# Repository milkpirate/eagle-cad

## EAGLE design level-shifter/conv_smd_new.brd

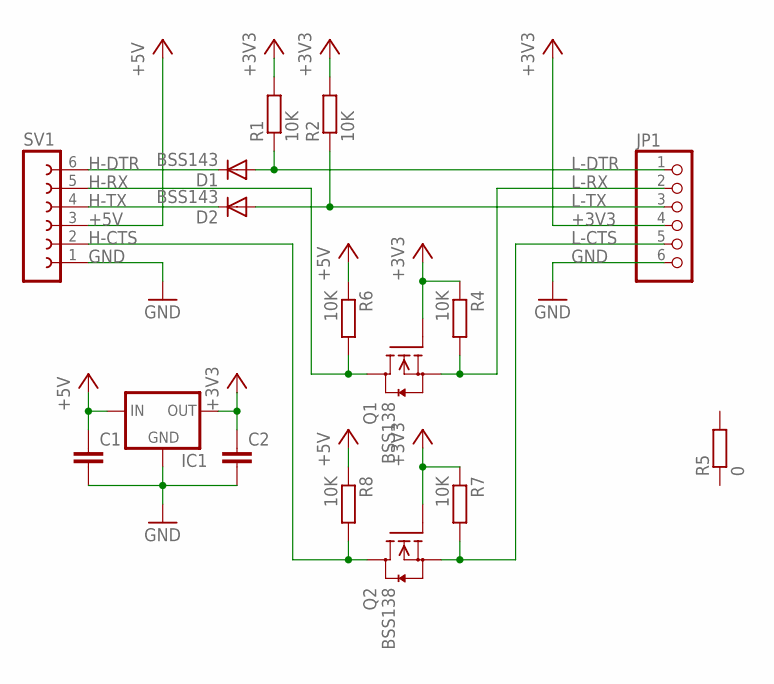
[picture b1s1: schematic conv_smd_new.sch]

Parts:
C1, C2: C-EUC0805; C0805
D1, D2: BSS143; SOD80C
IC1: MCP1700_SOT-32; SOT23
JP1: PINHD-1X6/90; 1X06/90
Q1, Q2: BSS138; SOT23
R1, R2, R4, R6, R7, R8: 10K; M0805
R5: 0; M1206
SV1: FE06W

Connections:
+3V3: C2.1, IC1.2 (OUT), JP1.4, Q1.1 (G), Q2.1 (G), R1.2, R2.2, R4.1, R7.1
+5V: C1.1, IC1.3 (IN), R6.1, R8.1, SV1.3
GND: C1.2, C2.2, IC1.1 (GND), JP1.6, SV1.1
H-CTS: Q2.3 (D), R8.2, SV1.2
H-DTR: D1.C, SV1.6
H-RX: Q1.3 (D), R6.2, SV1.5
H-TX: D2.C, SV1.4
L-CTS: JP1.5, Q2.2 (S), R7.2
L-DTR: D1.A, JP1.1, R1.1
L-RX: JP1.2, Q1.2 (S), R4.2
L-TX: D2.A, JP1.3, R2.1

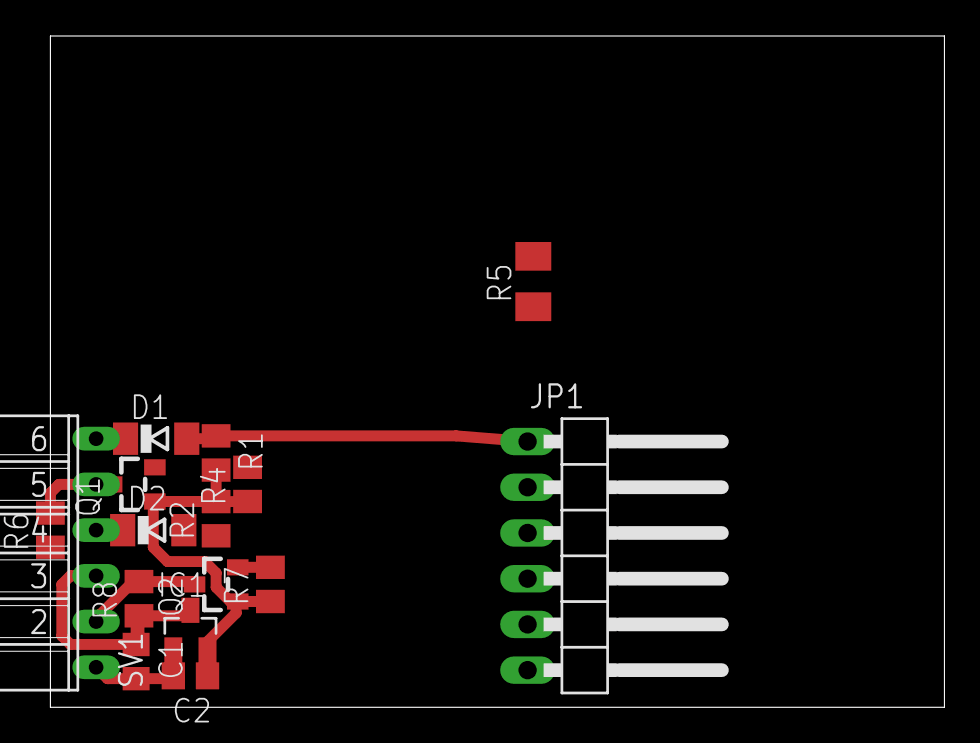
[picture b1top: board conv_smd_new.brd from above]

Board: 2 copper layers, 49.7 x 37.3 mm, 16 parts (0 on the bottom side), 11 nets.

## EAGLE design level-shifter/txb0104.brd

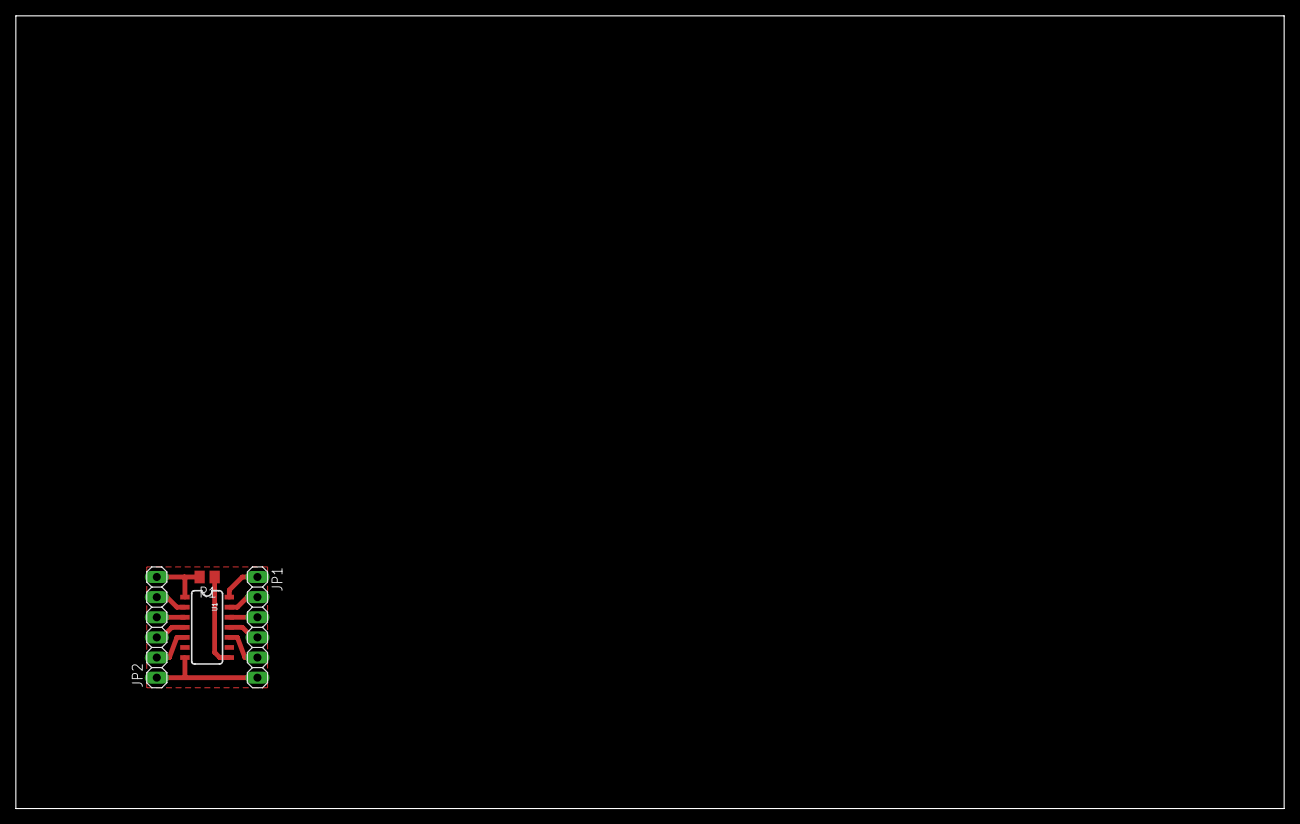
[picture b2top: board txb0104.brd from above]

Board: 2 copper layers, 160.0 x 100.0 mm, 4 parts (0 on the bottom side), 12 nets.

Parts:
JP1, JP2: 1X06
R1: M0805
U1: SO14

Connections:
GND: JP1.6, JP2.1, U1.7
unnamed: JP1.2, U1.13
unnamed: JP1.3, U1.12
unnamed: JP1.4, U1.11
unnamed: JP1.5, U1.10
unnamed: JP2.2, U1.5
unnamed: JP2.3, U1.4
unnamed: JP2.4, U1.3
unnamed: JP2.5, U1.2
unnamed: JP1.1, U1.14
unnamed: JP2.6, R1.2, U1.1
unnamed: R1.1, U1.8

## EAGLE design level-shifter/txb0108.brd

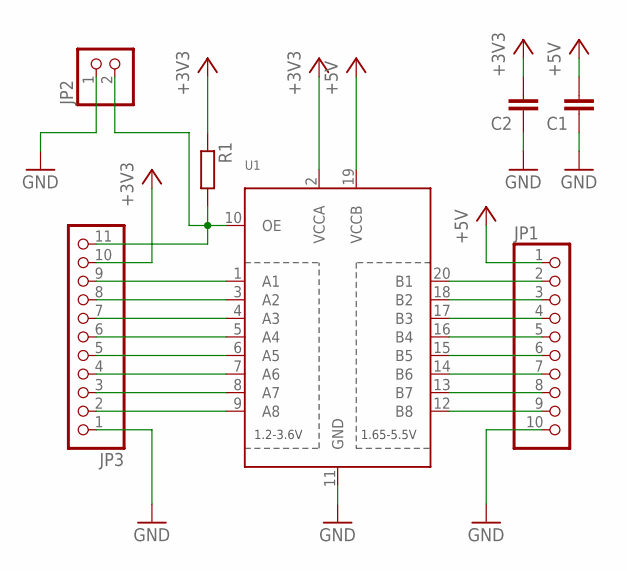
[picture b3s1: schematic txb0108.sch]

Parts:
C1: C-EUC0805K; C0805K
C2: C-EUC1206; C1206
JP1: PINHD-1X10; 1X10
JP2: PINHD-1X2; 1X02
JP3: PINHD-1X11; 1X11
R1: R-EU_M0805; M0805
U1: TXB0108PWR; TSSOP20

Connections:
+3V3: C2.2, JP3.10, R1.1, U1.2 (VCCA)
+5V: C1.2, JP1.1, U1.19 (VCCB)
GND: C1.1, C2.1, JP1.10, JP2.1, JP3.1, U1.11 (GND)
unnamed: JP1.2, U1.20 (B1)
unnamed: JP1.3, U1.18 (B2)
unnamed: JP1.4, U1.17 (B3)
unnamed: JP1.5, U1.16 (B4)
unnamed: JP1.6, U1.15 (B5)
unnamed: JP1.7, U1.14 (B6)
unnamed: JP1.8, U1.13 (B7)
unnamed: JP1.9, U1.12 (B8)
unnamed: JP3.2, U1.9 (A8)
unnamed: JP3.3, U1.8 (A7)
unnamed: JP3.4, U1.7 (A6)
unnamed: JP3.5, U1.6 (A5)
unnamed: JP3.6, U1.5 (A4)
unnamed: JP3.7, U1.4 (A3)
unnamed: JP3.8, U1.3 (A2)
unnamed: JP3.9, U1.1 (A1)
unnamed: JP2.2, JP3.11, R1.2, U1.10 (OE)

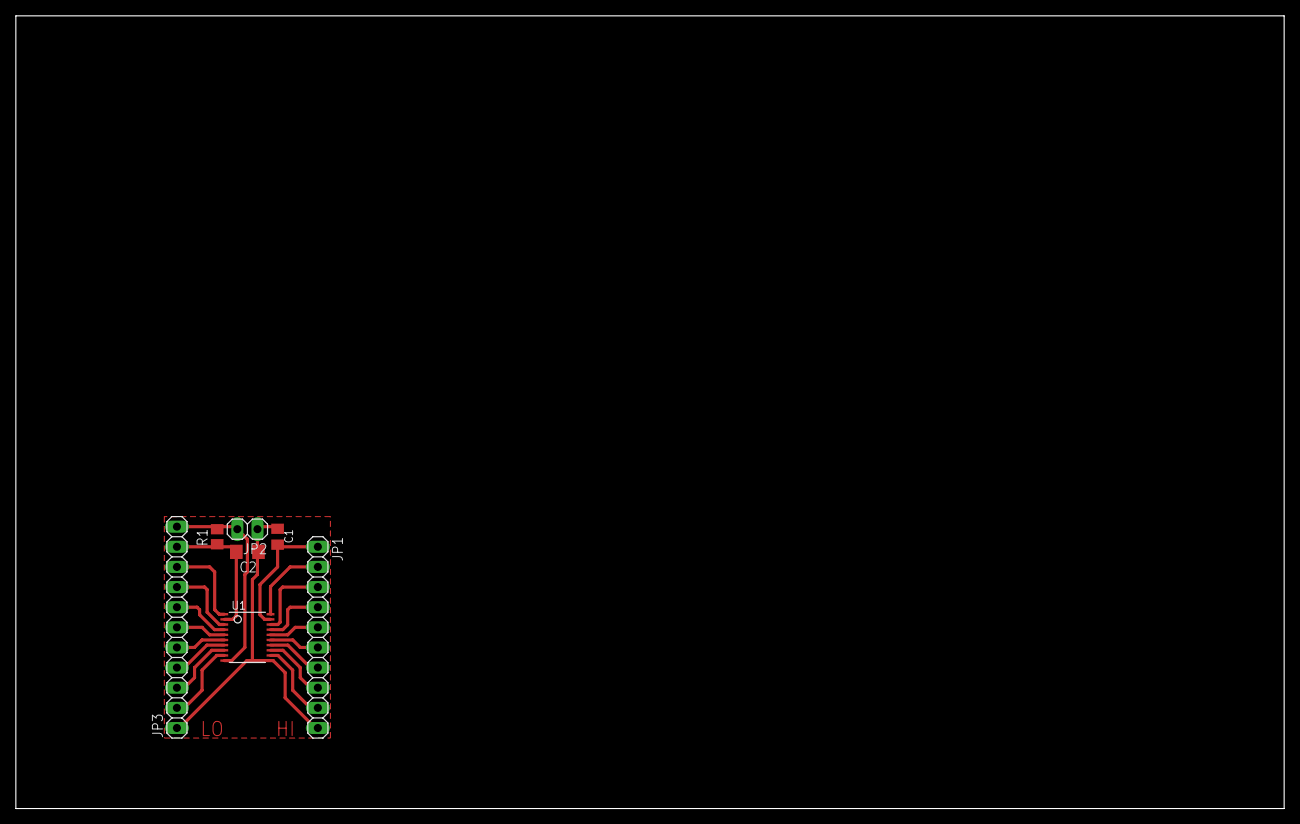
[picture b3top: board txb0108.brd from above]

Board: 2 copper layers, 160.0 x 100.0 mm, 7 parts (0 on the bottom side), 20 nets.

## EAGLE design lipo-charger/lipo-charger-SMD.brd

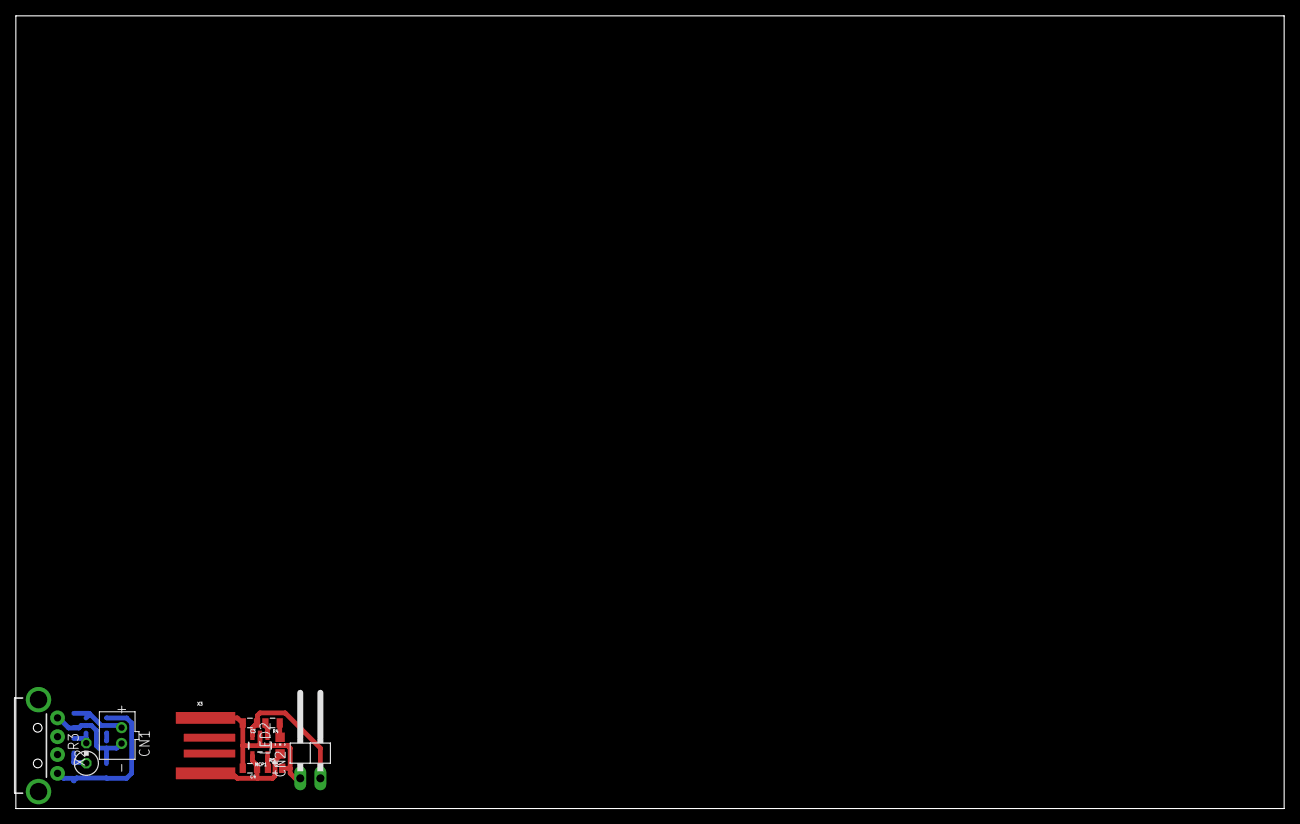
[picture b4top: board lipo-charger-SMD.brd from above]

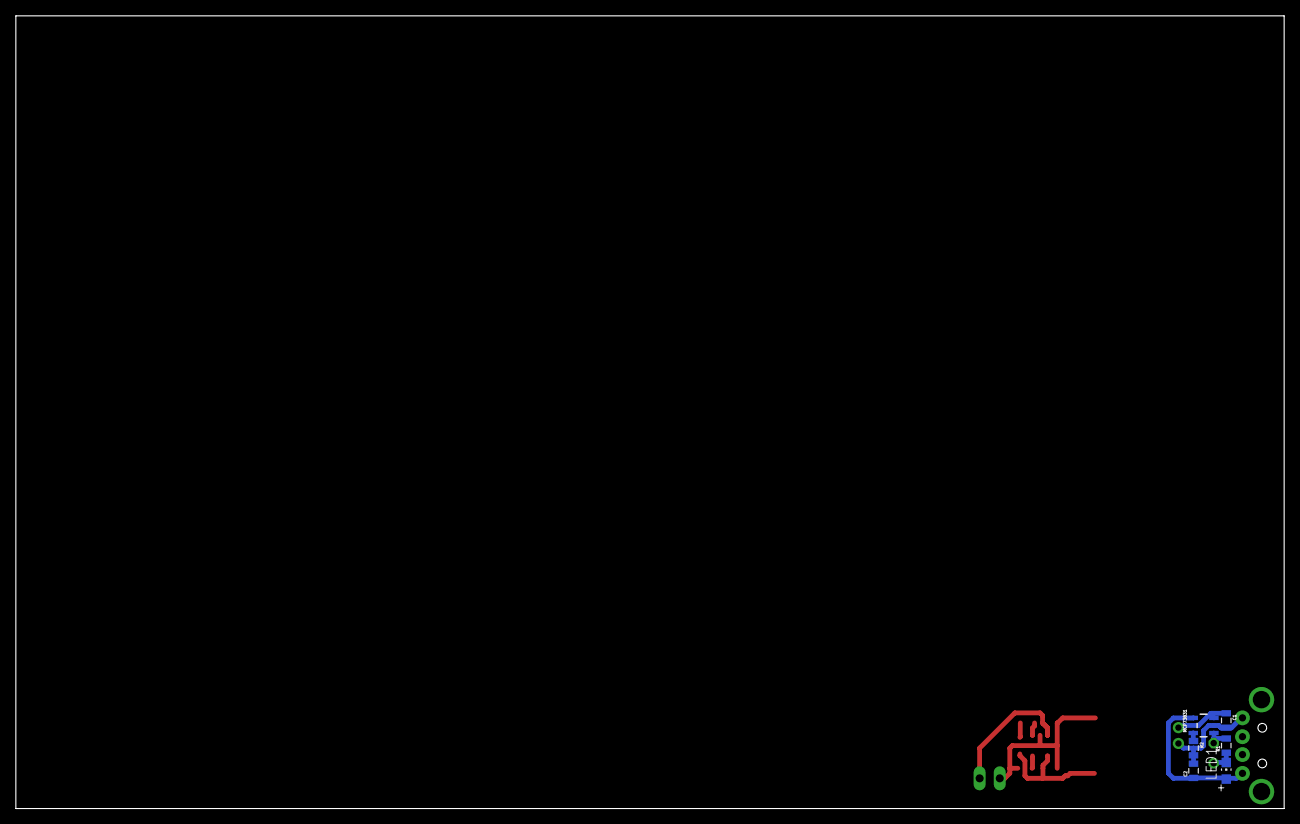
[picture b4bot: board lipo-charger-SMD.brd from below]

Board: 2 copper layers, 160.0 x 100.0 mm, 17 parts (6 on the bottom side), 10 nets.

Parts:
C1, C2, C3, C4: 4.7uF; 0805
CN1: JST-PH-2-THM
CN2: 1X02/90
LED1, LED2: CHIP-LED0805
MCP1, MCP73831: SOT23-5
R1, R4: 470ohm; 0805
R2, R5: 2k ohm; 0805
R3: 470ohm; 0309V
X2: USB-A-H
X3: USBPCB; USB-A-PCB

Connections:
GND: C1.2, C2.2, C3.2, C4.2, CN1.2, CN2.1, MCP1.2, MCP73831.2, R2.2, R5.2, X2.GND, X3.GND
unnamed: MCP73831.5, R2.1
unnamed: MCP1.5, R5.1
unnamed: C1.1, CN1.1, MCP73831.3
unnamed: LED1.C, R1.1, R3.1
unnamed: MCP73831.1, R1.2, R3.2
unnamed: C3.1, CN2.2, MCP1.3
unnamed: LED2.C, R4.1
unnamed: MCP1.1, R4.2
VCC: C2.1, C4.1, LED1.A, LED2.A, MCP1.4, MCP73831.4, X2.VBUS, X3.5V

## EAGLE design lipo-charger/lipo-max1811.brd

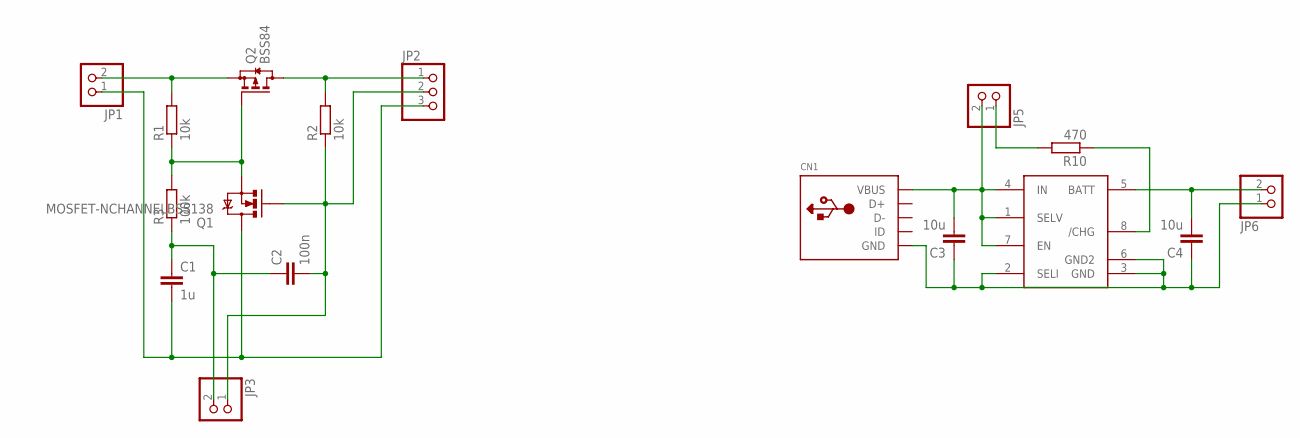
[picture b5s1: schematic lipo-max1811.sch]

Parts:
C1: 1u; C0805K
C2: 100n; C0805K
C3, C4: 10u; C0805K
CN1: USBTHM; USB-MINIB-THM
JP1, JP3, JP5, JP6: PINHD-1X2; 1X02
JP2: PINHD-1X3; 1X03
Q1: MOSFET-NCHANNELBSS138; SOT23
Q2: BSS84; SOT23
R1: 10k; R0805
R2: 10k; M0805
R3: 100k; R0805
R10: 470; M0805
U$1: MAX1811SO8; SO08

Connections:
BAT+: JP1.2, Q2.2 (S), R1.2
GND: C1.2, JP1.1, JP2.3, Q1.3 (D)
unnamed: C3.2, CN1.VBUS, JP5.2, U$1.1 (SELV), U$1.4 (IN), U$1.7 (EN)
unnamed: C3.1, C4.1, CN1.GND, JP6.1, U$1.2 (SELI), U$1.3 (GND), U$1.6 (GND2)
unnamed: Q1.2 (S), Q2.1 (G), R1.1, R3.2
unnamed: C1.1, C2.1, JP3.2, R3.1
unnamed: R10.1, U$1.8 (/CHG)
unnamed: C2.2, JP2.2, JP3.1, Q1.1 (G), R2.1
unnamed: JP5.1, R10.2
unnamed: C4.2, JP6.2, U$1.5 (BATT)
VCC: JP2.1, Q2.3 (D), R2.2

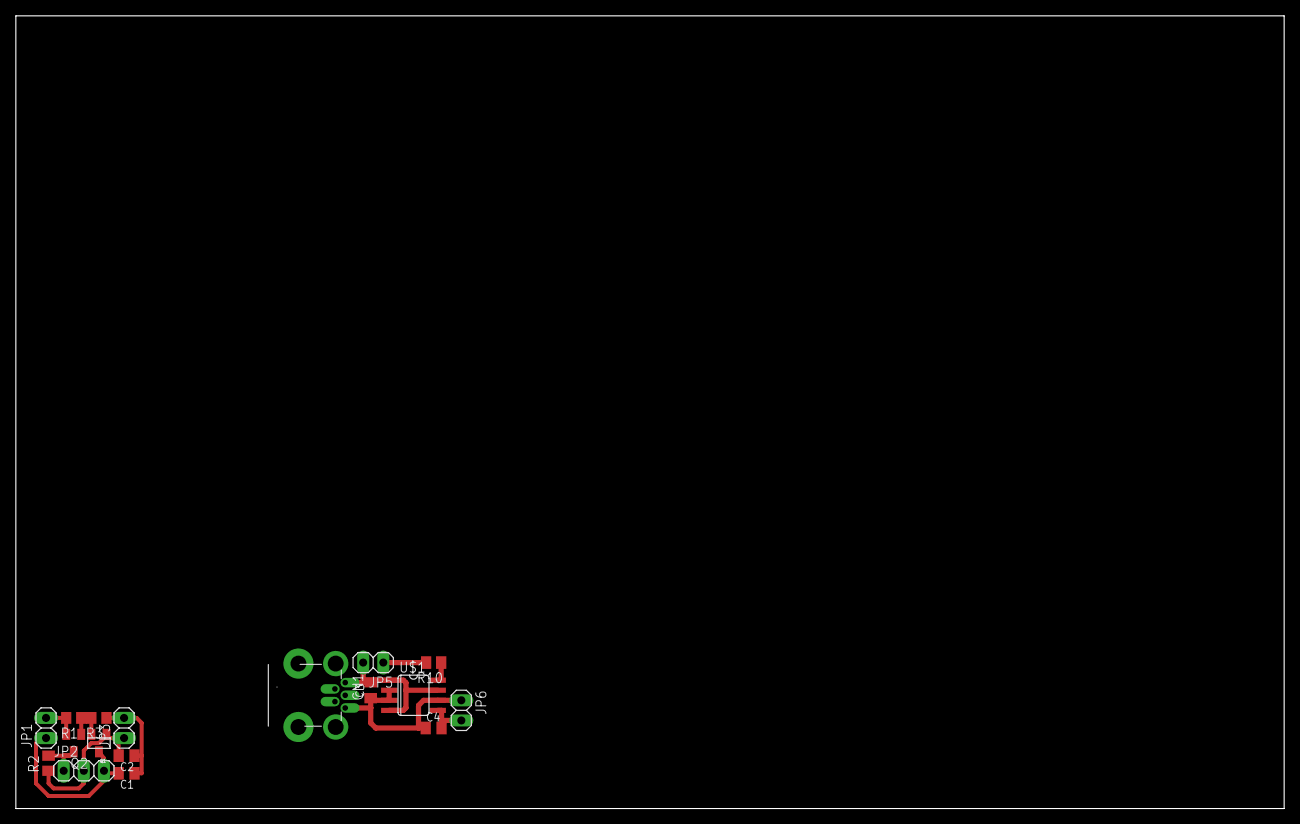
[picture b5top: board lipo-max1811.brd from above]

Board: 2 copper layers, 160.0 x 100.0 mm, 17 parts (0 on the bottom side), 11 nets.

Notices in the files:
parts and their libraries:
m-pad-2.1: License : GNU General Public License version 2 (see bottom)
SparkFun-DigitalIC: Licensing: Creative Commons ShareAlike 4.0 International - https://creativecommons.org/licenses/by-sa/4.0
